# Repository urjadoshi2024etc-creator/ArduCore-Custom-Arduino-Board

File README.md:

<div align="center">

# ⚡ ArduCore

### My Own Arduino Development Board

</div>

---

### So Why did I make a PCB named ArduCore?

I wanted to go one step deeper.

> Instead of using a ready-made Arduino board, I designed the **microcontroller circuit, power section, reset circuit, clock circuit, headers, and PCB layout myself**.

> I wanted my own Arduino Devboard so made this project 

---
### Schematic

<br><br>

### PCB Layout

<br><br>

### 3D PCB View

</div>
---
## Programming

### Arduino ISP
ArduCore does **not** contain a dedicated USB-to-Serial programmer.
> Instead, another Arduino can be used as an **ISP programmer**.

```bash
┌───────────────────────┐
│   Arduino Programmer  │
│                       │
│     ArduinoISP        │
└───────────┬───────────┘
            │
            │ ISP
            │
            ▼
┌───────────────────────┐
│       ArduCore        │
│                       │
│     ATmega328P        │
└───────────────────────┘
```

### Detailed instructions:
[`Programming ArduCore with Arduino ISP`](documentation/Arduino-ISP.md)

---

## 🎥 Project Demo

Yet to be implemented 

---

## Manufacturing
Manufacturing files are available in:

```bash
production/gerbers/
```

### Gerber Package
[`ArduCore-Gerbers.zip`](production/gerbers/ArduCore-Gerbers.zip)

---

## Bill of Materials
The complete component list is maintained in:

```bash
production/bom/
```
### BOM
[`ArduCore-BOM.csv`](production/bom/ArduCore-BOM.csv)

---
## Grant Budget ($25 B-Tier)

This project is submitted under the **B-Tier ($25 max)** hardware grant for custom development boards.

### Cost Breakdown

| Item | Description | Estimated Cost |
| :--- | :--- | :--- |
| **PCB Fabrication** | Custom 2-layer PCB (5 pcs) via JLCPCB | ~$2.00 |
| **Shipping & Handling** | Standard global shipping for manufactured PCBs | ~$10.50 |
| **Component BOM** | ATmega328P-PU, 16 MHz Crystal, 7805 regulator, THT passives, switches, & pin headers | ~$6.50 |
| **Total Requested** | | **$19.00** |

---

## Tools I Used
1. Kicad
2. Arduino IDE
4. Github

--- This project started with a simple question ---

> **"What's actually inside an Arduino?"**

### Build it. Break it. Understand it. Improve it.

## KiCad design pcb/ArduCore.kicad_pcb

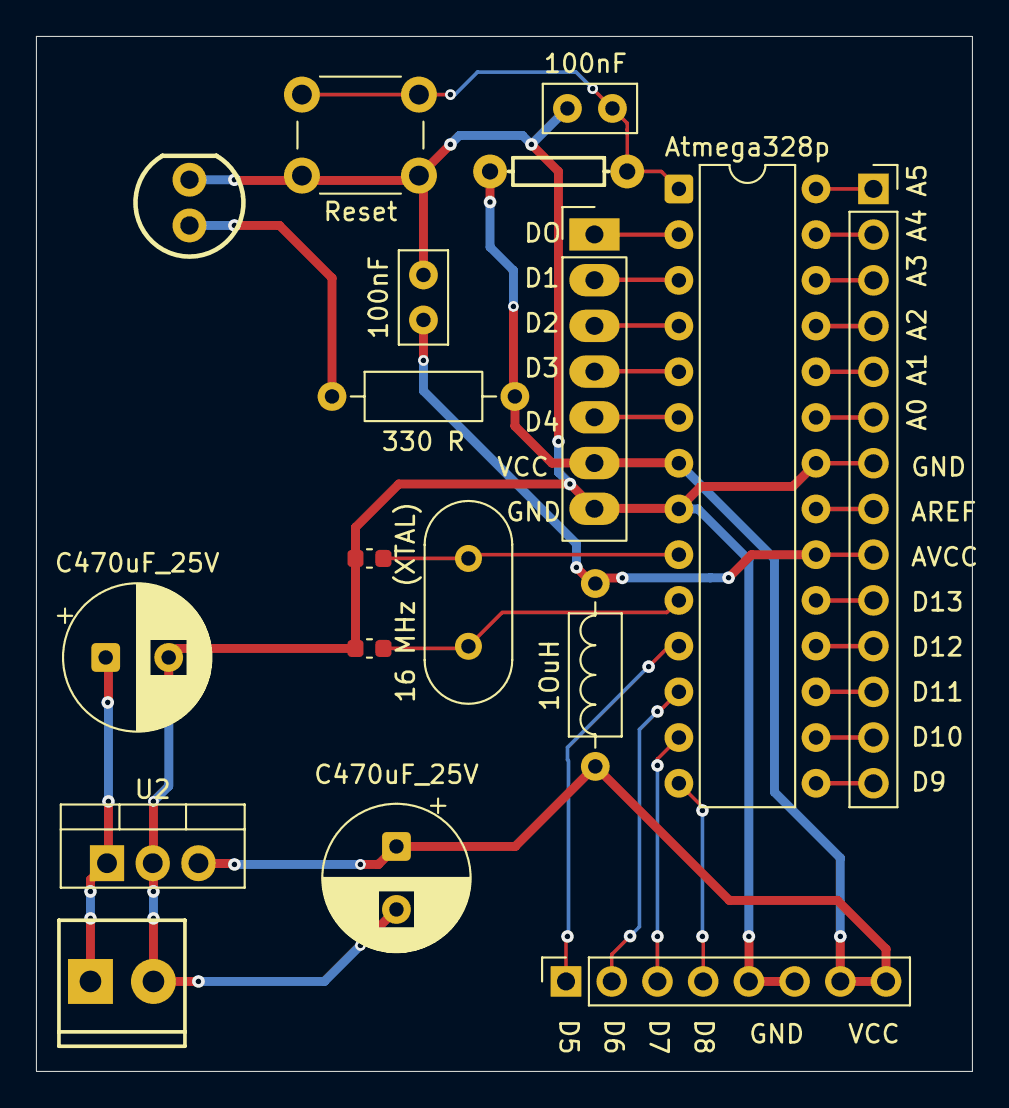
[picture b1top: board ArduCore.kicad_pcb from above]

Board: 2 copper layers, 52.0 x 57.5 mm, 18 parts (0 on the bottom side), 29 nets.

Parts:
1OuH: 10uH_5x5mm_1.0A; L_Axial_L6.6mm_D2.7mm_P10.16mm_Horizontal_Vishay_IM-2
16 MHz (XTAL): Crystal_16MHz; Crystal_HC49-4H_Vertical
100nF, 100nF#2: 100nF_Ceramic; C_Disc_D5.0mm_W2.5mm_P2.50mm
330 R: 330 R; R_Axial_DIN0207_L6.3mm_D2.5mm_P10.16mm_Horizontal
Atmega328p: ATmega328P-P; DIP-28_W7.62mm
C3, C4: 22nF; C_0603_1608Metric
C470uF_25V, C470uF_25V#2: 470uF_25V; CP_Radial_D8.0mm_P3.50mm
D1: Red; LED_5mm_PTH_Red_Silk
J1: Conn_01x07_Pin; PinHeader_1x07_P2.54mm_Vertical
J2: Conn_01x14_Pin; PinSocket_1x14_P2.54mm_Vertical
J3: Conn_01x08_Pin; PinSocket_1x08_P2.54mm_Vertical
J4: Ext_supply; ScrewTerminal_1x02_P3.5mm_Horizontal_Black
R1: 10k; R_Axial_DIN0207_L6.3mm_D2.5mm_P7.62mm_Horizontal
Reset: Push_Button; SW_PUSH_6mm
U2: AS7805AT-G1; TO-220-3_Vertical

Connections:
0: Atmega328p.2 (PD0), J1.1
1: Atmega328p.3 (PD1), J1.2
2: Atmega328p.4 (PD2), J1.3
3: Atmega328p.5 (PD3), J1.4
4: Atmega328p.6 (PD4), J1.5
5: Atmega328p.11 (PD5), J3.1
6: Atmega328p.12 (PD6), J3.2
7: Atmega328p.13 (PD7), J3.3
8: Atmega328p.14 (PB0), J3.4
9: Atmega328p.15 (PB1), J2.14
10: Atmega328p.16 (PB2), J2.13
11: Atmega328p.17 (PB3), J2.12
12: Atmega328p.18 (PB4), J2.11
13: Atmega328p.19 (PB5), J2.10
A0: Atmega328p.23 (PC0), J2.6
A1: Atmega328p.24 (PC1), J2.5
A2: Atmega328p.25 (PC2), J2.4
A3: Atmega328p.26 (PC3), J2.3
A4: Atmega328p.27 (PC4), J2.2
A5: Atmega328p.28 (PC5), J2.1
AREF: Atmega328p.21 (AREF), J2.8
AVCC: 1OuH.2, 100nF.1, Atmega328p.20 (AVCC), J2.9
GND: 100nF.2, 100nF#2.2, Atmega328p.8 (GND), Atmega328p.22 (GND), C3.1, C4.2, C470uF_25V.2, C470uF_25V#2.2, D1.1 (K), J1.7, J2.7, J3.5, J3.6, J4.2, Reset.1, U2.2
unnamed: 330 R.1, D1.2 (A)
unnamed: C470uF_25V#2.1, J4.1, U2.1 (IN)
unnamed: 16 MHz (XTAL).2, Atmega328p.9 (XTAL1/PB6), C4.1
unnamed: 16 MHz (XTAL).1, Atmega328p.10 (XTAL2/PB7), C3.2
Reset: 100nF#2.1, Atmega328p.1 (~RESET/PC6), R1.2, Reset.2
VCC: 1OuH.1, 330 R.2, Atmega328p.7 (VCC), C470uF_25V.1, J1.6, J3.7, J3.8, R1.1, U2.3 (OUT)
